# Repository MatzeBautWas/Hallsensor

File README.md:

# Hallsensor
Hallsensor PCB to detect gear revolutions in a Pistontank of a model submarine

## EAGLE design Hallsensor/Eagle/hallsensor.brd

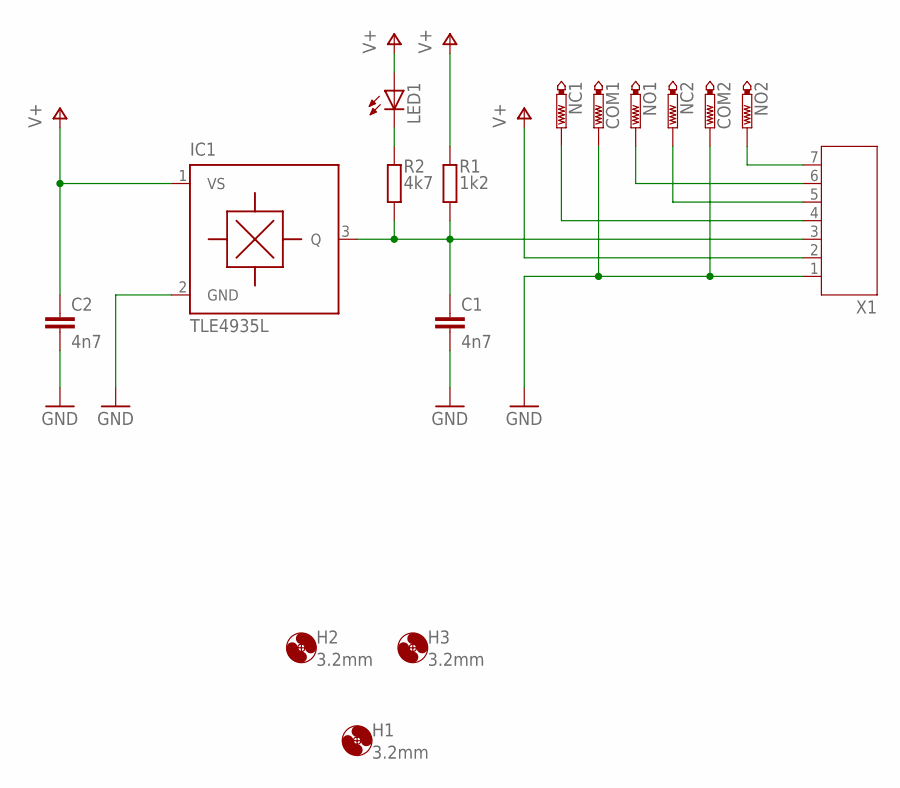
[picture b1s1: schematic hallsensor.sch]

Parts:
C1, C2: 4n7; C0805
COM1, COM2: PTR1PAD1-13Y; P1-13Y
H1, H2, H3: 3.2mm; 3,2
IC1: TLE4935L; PG-SSO-3-2
LED1: LED3MM
NC1, NC2: PTR1PAD1-13Y; P1-13Y
NO1, NO2: PTR1PAD1-13Y; P1-13Y
R1: 1k2; R0805
R2: 4k7; R0805
X1: JST-PH7

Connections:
GND: C1.2, C2.2, COM1.1, COM2.1, IC1.2 (GND), X1.1
unnamed: LED1.K (C), R2.2
unnamed: NC1.1, X1.4
unnamed: NO1.1, X1.6
unnamed: NC2.1, X1.5
unnamed: NO2.1, X1.7
OUT: C1.1, IC1.3 (Q), R1.1, R2.1, X1.3
V+: C2.1, IC1.1 (VS), LED1.A, R1.2, X1.2

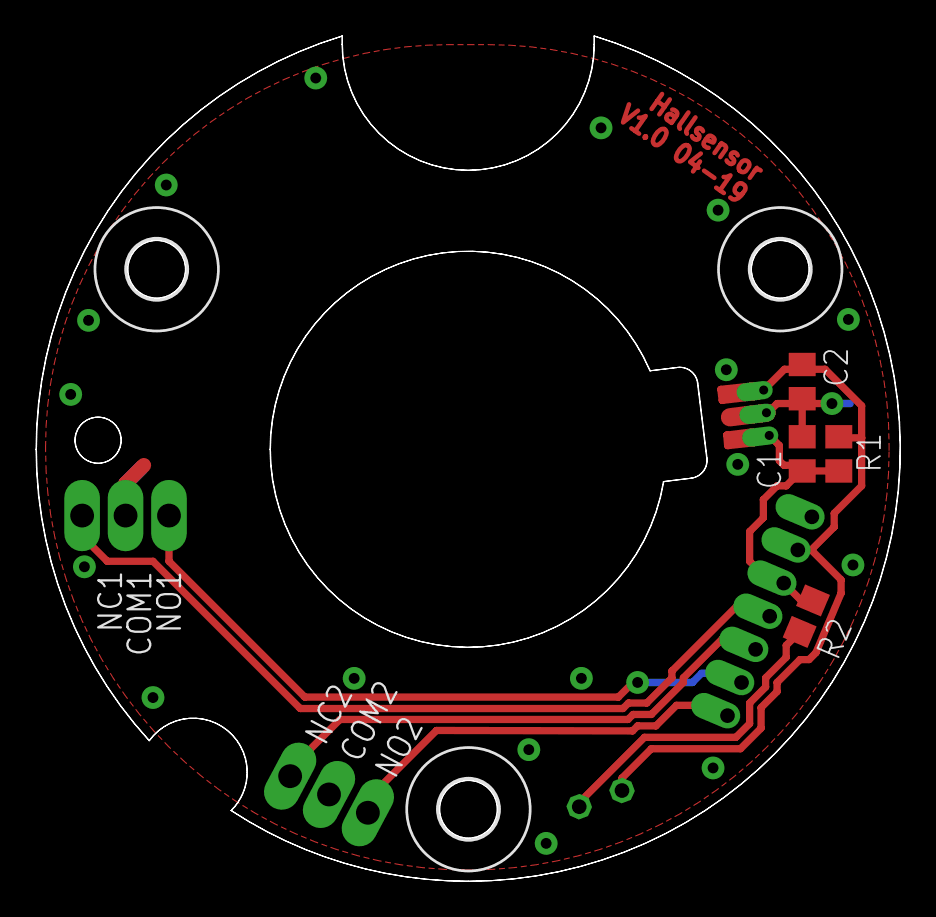
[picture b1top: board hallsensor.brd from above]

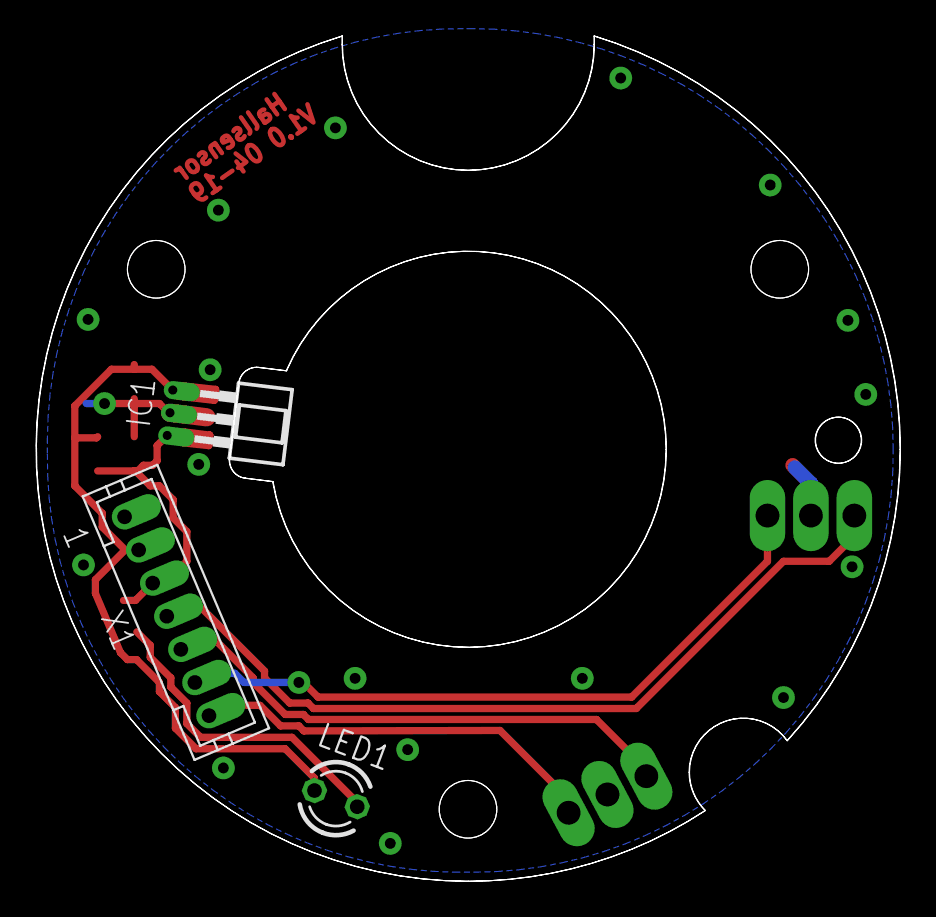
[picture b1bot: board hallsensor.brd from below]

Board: 2 copper layers, 48.0 x 47.0 mm, 16 parts (3 on the bottom side), 8 nets.
